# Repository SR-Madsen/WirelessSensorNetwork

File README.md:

# Wireless Sensor Network
STM32-based project for testing Internet of Things, Ethernet, RFID, and similar technologies.

## Repository Structure
This repository contains a folder for documentation, which includes datasheets and reference manuals used during the design phase as well as other tools and general documents. Additionally, there are folders for the Master board and Slave board. These further includes demo programs used for testing functionality that is possible to test on either the STM32F769-DISCO, STM32L412 Nucleo, or STM32WB55 Nucleo boards. The actual program used for each board is placed in a separate, aptly named, folder. The PCBs themselves are also found as KiCad projects within either the Master or Slave folder.

## Overview
The project will contain one large Master board with many functionalities and several small Slaves only used for measuring sensor values. The slaves are powered by a coin-cell battery, and will thus be in sleep mode most of the time. Occasionally, they will wake and retrieve sensor measurements, which are transmitted over 2.4 GHz ZigBee to the Master. The Master is supplied through USB and will, aside from receiving data from the Slaves, contain an RFID antenna used for detecting valid cards/keys, which allow the user to initiate a data transfer. This data transfer may be through USB or Ethernet, as the Master will host a small webpage containing the data from each Slave.

A full block diagram of the project can be found as draw.io files in the Documentation folder, but is also shown below. In the documentation folder, a LaTeX report can also be found.

## Hardware
The designed PCBs are shown below.

## Software
By using ST development kits and the STM32Cube ecosystem, preliminary software has been created for both the master and slave.

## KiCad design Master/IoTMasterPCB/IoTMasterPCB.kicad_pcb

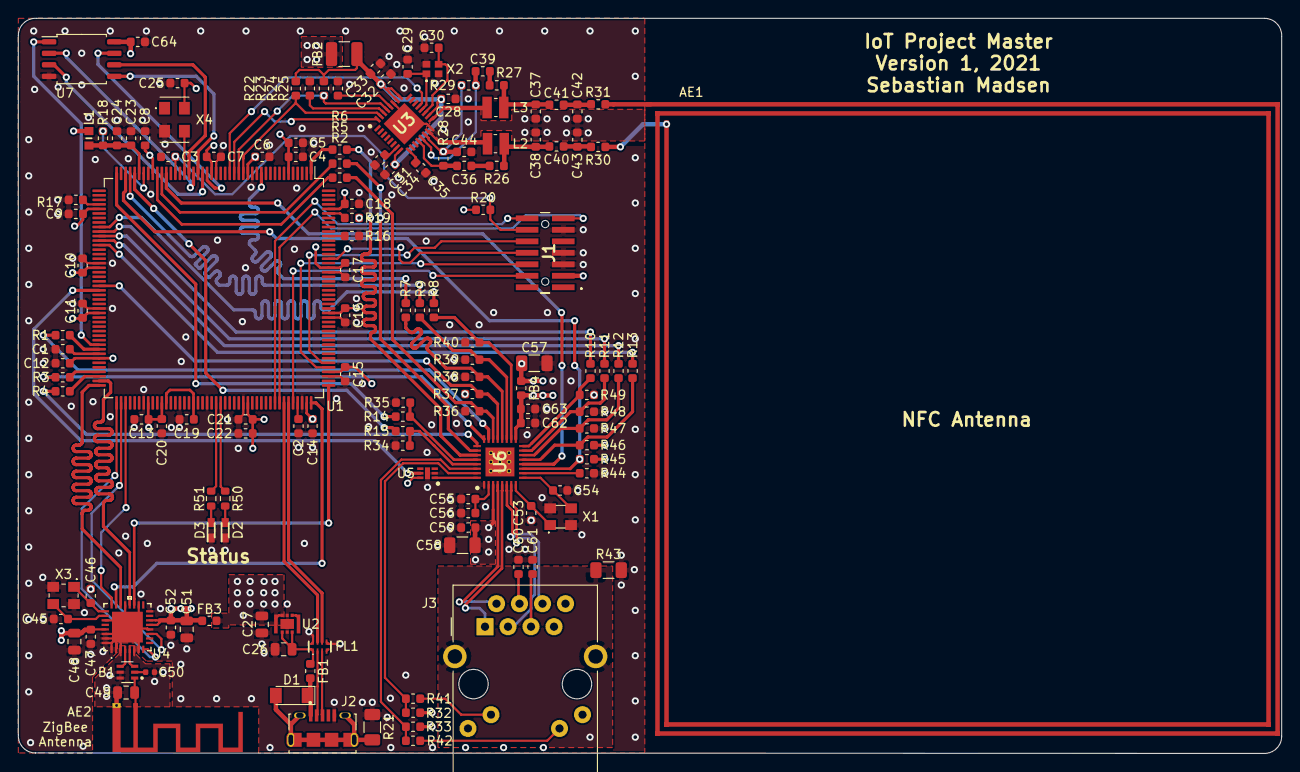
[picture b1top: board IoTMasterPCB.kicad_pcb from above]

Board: 4 copper layers, 139.5 x 81.2 mm, 143 parts (0 on the bottom side), 125 nets.

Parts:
AE1: NFC 13.56 MHz; NXP_NFC_13.56MHz
AE2: On-PCB; Texas_SWRA117D_2.4GHz_Left
B1: 2450FB15L0001E
C1, C2, C19: 2.2 µF; C_0603_1608Metric
C3, C4, C6, C7, C8, C9, C10, C11, C12, C13, C14, C15, C16, C17, C18, C20, C21, C23, C25, C28, C32, C34, C44, C47, C52, C64: 100 nF; C_0603_1608Metric
C5: 10 µF; C_0603_1608Metric
C22, C24, C33: 1 µF; C_0603_1608Metric
C26: 4.7 µF; C_0805_2012Metric
C27, C48, C51: 10 µF; C_0805_2012Metric
C29, C30: 15 pF; C_0603_1608Metric
C31, C35: 470 nF; C_0603_1608Metric
C36, C39: 1 nF; C_0603_1608Metric
C37, C38: 120 pF; C_0603_1608Metric
C40, C41: 56 pF; C_0603_1608Metric
C42, C43: 220 pF; C_0603_1608Metric
C45, C46: 22 pF; C_0603_1608Metric
C49: RF_MATCH; C_0805_2012Metric
C50: 22 pF C0G; C_0402_1005Metric
C53, C54: 27pF; C_0603_1608Metric
C55: 2.2uF; C_0603_1608Metric
C56, C59, C60, C61, C62: 100nF; C_0603_1608Metric
C57, C58: 22uF; C_1206_3216Metric
C63: 22uF; C_0603_1608Metric
D1: 5.6 V; D_MiniMELF
D2: 150060SS55040; 150060VS55040
D3: 150060VS55040
FB1: 120 @ 100 MHz; L_0603_1608Metric
FB2: 600R @ 100 MHz; L_1210_3225Metric
FB3: 600R @ 100 MHz; L_0603_1608Metric
FB4: 220R @ 100 MHz; L_0603_1608Metric
FL1: ECMF02-4CMX8; ECMF024CMX8
J1: M50-3610742R
J2: 10118194-0001LF
J3: RJMG1BD3B8K1ANR
L1: BK1608HS601-T
L2, L3: 470 nH; SRN2512R47M
R1, R2, R3, R4, R5, R6, R7, R8, R9, R10, R11, R12, R13, R14, R15: 33; R_0603_1608Metric
R16, R17, R19, R20: 10 kOhm; R_0603_1608Metric
R18: 47 Ohm; R_0603_1608Metric
R21: 0R; R_1206_3216Metric
R22, R23: 10k; R_0603_1608Metric
R24, R25, R32, R33, R37, R45, R46: 4.7k; R_0603_1608Metric
R26, R27: 12k; R_0603_1608Metric
R28, R29, R34, R35, R36, R38, R39, R40, R47, R48, R49: 1k; R_0603_1608Metric
R30, R31: 1.43; R_0603_1608Metric
R41, R42: 300; R_0603_1608Metric
R43: 0; R_1206_3216Metric
R44: 6.49k; R_0603_1608Metric
R50, R51: 150; R_0603_1608Metric
U1: STM32F469IITx; LQFP-176_24x24mm_P0.5mm
U2: MYRGP330100B21RA; MYRGP180100B21RA
U3: CLRC66303HNY
U4: AT86RF232-ZX
U5: MIC826TYMT-TR
U6: KSZ8081MNX
U7: W25Q32JVSS; SOIC-8_5.23x5.23mm_P1.27mm
X1: ECS-250-18-33B-CKY-TR; ECS-250-18-33B-CKY
X2: 27.12 MHz; ECS27121037AGNTR
X3: 16 MHz; ECS1601633BCKMTR
X4: ECS-5032MV-100-CN-TR; ECS5032MV250CNTR

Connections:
+3V3: C4.2, C5.2, C6.2, C7.2, C8.2, C9.2, C10.2, C11.2, C12.2, C13.2, C14.2, C15.2, C16.2, C17.2, C18.1, C20.2, C21.1, C22.1, C25.1, C27.2, C57.2, C64.2, FB2.2, FB3.2, FB4.1, J1.3, J3.L1, J3.L4, L1.1, R19.1, R20.1, U1.6, U1.15, U1.23, U1.36, U1.49, U1.62, U1.72, U1.82, U1.96, U1.99, U1.118, U1.131, U1.136, U1.149, U1.159, U1.172, U2.3, U2.8, U5.6, U7.8, X4.4
+5V: C26.2, FB1.1, FL1.1, U2.4, U2.6
/Ethernet/COL: R14.2, R35.2, U6.28
/Ethernet/CRS: R15.2, R34.2, U6.29
/Ethernet/LED1: R33.2, R42.2, U6.30
/Ethernet/LED2: R32.2, R41.2, U6.31
/Ethernet/RST: U5.1, U6.32
/Ethernet/RXD0: R10.2, R49.2, U6.16
/Ethernet/RXD1: R11.2, R48.2, U6.15
/Ethernet/RXD2: R12.2, R47.2, U6.14
/Ethernet/RXD3: R13.2, R46.2, U6.13
/Ethernet/RXN: J3.R6, U6.6
/Ethernet/RXP: J3.R3, U6.7
/Ethernet/RX_CLK: R9.2, R39.2, U6.19
/Ethernet/RX_DV: R8.2, R40.2, U6.18
/Ethernet/RX_ER: R7.2, R38.2, U6.20
/Ethernet/TXD0: R3.2, U6.24
/Ethernet/TXD1: R4.2, U6.25
/Ethernet/TXD2: R5.2, U6.26
/Ethernet/TXD3: R6.2, U6.27
/Ethernet/TXN: J3.R2, U6.4
/Ethernet/TXP: J3.R1, U6.5
/Ethernet/TX_CLK: R2.2, R36.2, U6.22
/Ethernet/TX_EN: R1.2, U6.23
/Ethernet/VDDA: C58.2, C59.1, C62.1, C63.1, FB4.2, R32.1, R33.1, R37.1, R45.1, R46.1, U6.3, U6.17
/Ethernet/XI: C54.1, U6.9, X1.3
/Ethernet/XO: C53.1, U6.8, X1.1
/MCU/12DSI: C19.2, U1.100, U1.106
/MCU/ETH_COL: R14.1, U1.44
/MCU/ETH_CRS: R15.1, U1.40
/MCU/ETH_INT: R37.2, U1.66, U6.21
/MCU/ETH_MDC: U1.33, U6.12
/MCU/ETH_MDIO: R45.2, U1.42, U6.11
/MCU/ETH_RXD0: R10.1, U1.54
/MCU/ETH_RXD1: R11.1, U1.55
/MCU/ETH_RXD2: R12.1, U1.56
/MCU/ETH_RXD3: R13.1, U1.57
/MCU/ETH_RX_CLK: R9.1, U1.41
/MCU/ETH_RX_DV: R8.1, U1.53
/MCU/ETH_RX_ER: R7.1, U1.12
/MCU/ETH_TXD0: R3.1, U1.85
/MCU/ETH_TXD1: R4.1, U1.86
/MCU/ETH_TXD2: R5.1, U1.34
/MCU/ETH_TXD3: R6.1, U1.1
/MCU/ETH_TX_CLK: R2.1, U1.35
/MCU/ETH_TX_EN: R1.1, U1.80
/MCU/I2C2_SCL: R23.1, U1.17, U3.29
/MCU/I2C2_SDA: R22.1, U1.16, U3.31
/MCU/JTCK: J1.6, U1.137
/MCU/JTDI: J1.10, U1.138
/MCU/JTDO: J1.8, U1.161
/MCU/JTMS: J1.4, U1.128
/MCU/NRST: C3.2, J1.12, R20.2, U1.31
/MCU/OSC_IN: U1.29, X4.3
/MCU/QSPI_BK1_CLK: U1.28, U7.6
/MCU/QSPI_BK1_IO0: U1.26, U7.5
/MCU/QSPI_BK1_IO1: U1.27, U7.2
/MCU/QSPI_BK1_IO2: U1.25, U7.3
/MCU/QSPI_BK1_IO3: U1.24, U7.7
/MCU/SPI2_MISO: U1.87, U4.20
/MCU/SPI2_MOSI: U1.88, U4.22
/MCU/SPI2_SCK: U1.133, U4.19
/MCU/UART_RX: J1.13, U1.125
/MCU/UART_TX: J1.14, U1.124
/MCU/USB_DN: FL1.7, U1.126
/MCU/USB_DP: FL1.6, U1.127
/MCU/VDDA: C23.1, C24.1, L1.2, R18.1, U1.39
/MCU/~ETH_RESET: U1.67, U5.5
/MCU/~QSPI_BK1_NCS: U1.79, U7.1
/MCU/~SPI2_NSS: U1.132, U4.23
/RFID/IRQ: U1.18, U3.32
/RFID/NFC_3V3: C28.2, C32.2, C33.2, C34.1, FB2.1, R22.2, R23.2, U3.8, U3.18, U3.25, U3.26
/RFID/PDOWN: U1.19, U3.21
/RFID/RXN: C39.1, R29.2, U3.13
/RFID/RXP: C36.1, R28.1, U3.12
/RFID/VMID: C44.1, R28.2, R29.1, U3.14
/ZigBee/IRQ: U1.91, U4.24
/ZigBee/SLP_TR: U1.90, U4.11
/ZigBee/XI: C46.1, U4.25, X3.1
/ZigBee/XO: C45.2, U4.26, X3.3
/ZigBee/ZB_3V3: C47.2, C48.2, C51.1, C52.1, FB3.1, U4.13, U4.14, U4.29
/ZigBee/~RST: U1.89, U4.8
GND: AE2.2, B1.5, B1.6, C1.1, C2.1, C3.1, C4.1, C5.1, C6.1, C7.1, C8.1, C9.1, C10.1, C11.1, C12.1, C13.1, C14.1, C15.1, C16.1, C17.1, C18.2, C19.1, C20.1, C21.2, C22.2, C23.2, C24.2, C25.2, C26.1, C27.1, C28.1, C29.1, C30.1, C31.2, C32.1, C33.1, C34.2, C35.1, C37.1, C38.2, C42.1, C43.2, C44.2, C45.1, C46.2, C47.1, C48.1, C49.2, C50.2, C51.2, C52.2, C53.2, C54.2, C55.1, C56.1, C57.1, C58.1, C59.2, C60.2, C61.2, C62.2, C63.2, C64.1, D2.1, D3.1, FL1.5, FL1.8, J1.5, J1.7, J1.11, J2.5, J3.R8, R16.1, R17.1, R21.1, R24.1, R25.1, R34.1, R35.1, R36.1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
GND1: D1.2, J2.S1, R21.2
unnamed: AE1.1, R31.2
unnamed: AE1.2, R30.2
unnamed: AE2.1, B1.1, C49.1
unnamed: B1.2, C50.1
unnamed: B1.3, U4.5
unnamed: B1.4, U4.4
unnamed: C1.2, U1.81
unnamed: C2.2, U1.129
unnamed: C29.2, U3.20, X2.1
unnamed: C30.2, U3.19, X2.3
unnamed: C31.1, U3.7
unnamed: C35.2, U3.9
unnamed: C36.2, R26.2
unnamed: C37.2, C40.2, L2.1, R26.1
unnamed: C38.1, C41.2, L3.2, R27.2
unnamed: C39.2, R27.1
unnamed: C40.1, C42.2, R30.1
unnamed: C41.1, C43.1, R31.1
unnamed: C55.2, C56.2, U6.2
unnamed: C60.1, J3.R4
unnamed: C61.1, J3.R5
unnamed: D1.1, FB1.2, J2.1
unnamed: D2.2, R50.1
unnamed: D3.2, R51.1
unnamed: FL1.2, J2.2
unnamed: FL1.3, J2.3
unnamed: J3.13, R43.1
unnamed: J3.L2, R42.1
unnamed: J3.L3, R41.1
unnamed: L2.2, U3.15
unnamed: L3.1, U3.17
unnamed: R16.2, U1.166
unnamed: R17.2, U1.48
unnamed: R18.2, U1.38
unnamed: R19.2, U1.171
unnamed: R24.2, U3.30
unnamed: R25.2, U3.28
unnamed: R44.1, U6.10
unnamed: R50.2, U1.112
unnamed: R51.2, U1.111
unnamed: U2.1, U2.7

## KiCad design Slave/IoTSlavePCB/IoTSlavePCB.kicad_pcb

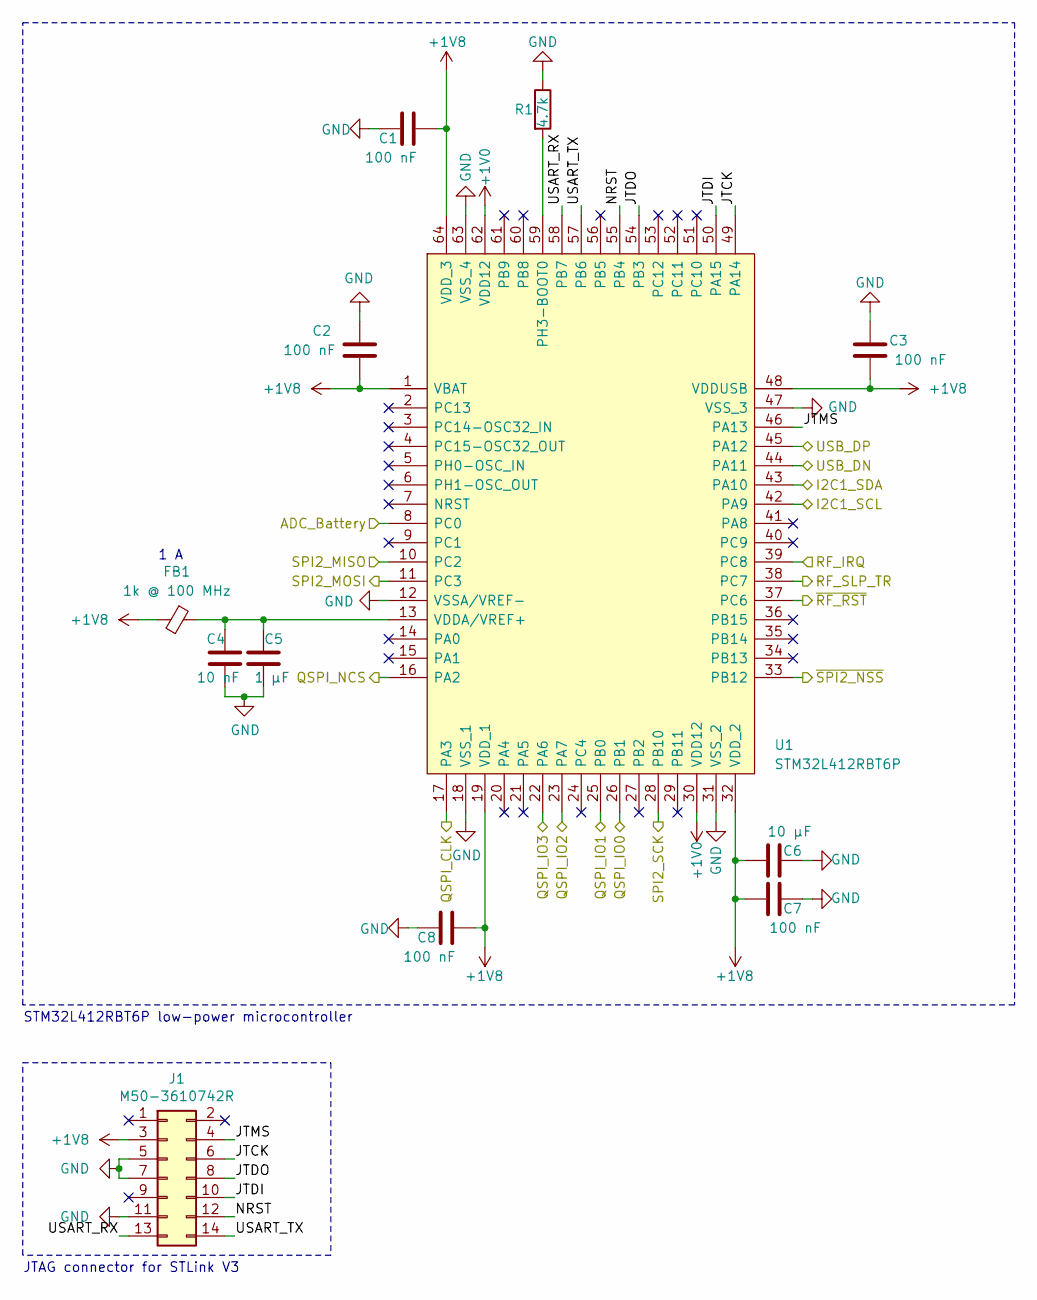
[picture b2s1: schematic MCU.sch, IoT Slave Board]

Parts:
C1, C2, C3, C7, C8: 100 nF; C_0603_1608Metric
C4: 10 nF; C_0603_1608Metric
C5: 1 µF; C_0805_2012Metric
C6: 10 µF; C_0805_2012Metric
FB1: 1k @ 100 MHz; L_0603_1608Metric
J1: M50-3610742R
R1: 4.7k; R_0603_1608Metric
U1: STM32L412RBT6P; Manufacturer_Part_Number STM32L412RBT6P; Mouser Part Number 511-STM32L412RBT6P

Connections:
+1V0: U1.30 (VDD12), U1.62 (VDD12); also elsewhere on the board
+1V8: C1.2, C2.2, C3.1, C6.1, C7.1, C8.2, FB1.2, J1.3, U1.1 (VBAT), U1.19 (VDD_1), U1.32 (VDD_2), U1.48 (VDDUSB), U1.64 (VDD_3); also elsewhere on the board
/MCU/ADC_Battery: U1.8 (PC0); also elsewhere on the board
/MCU/I2C1_SCL: U1.42 (PA9); also elsewhere on the board
/MCU/I2C1_SDA: U1.43 (PA10); also elsewhere on the board
/MCU/JTCK: J1.6, U1.49 (PA14)
/MCU/JTDI: J1.10, U1.50 (PA15)
/MCU/JTDO: J1.8, U1.54 (PB3)
/MCU/JTMS: J1.4, U1.46 (PA13)
/MCU/NRST: J1.12, U1.55 (PB4)
/MCU/QSPI_CLK: U1.17 (PA3); also elsewhere on the board
/MCU/QSPI_NCS: U1.16 (PA2); also elsewhere on the board
/MCU/RF_SLP_TR: U1.38 (PC7); also elsewhere on the board
/MCU/SPI2_MISO: U1.10 (PC2); also elsewhere on the board
/MCU/SPI2_MOSI: U1.11 (PC3); also elsewhere on the board
/MCU/SPI2_SCK: U1.28 (PB10); also elsewhere on the board
/MCU/USART_RX: J1.13, U1.58 (PB7)
/MCU/USART_TX: J1.14, U1.57 (PB6)
/MCU/USB_DN: U1.44 (PA11); also elsewhere on the board
/MCU/USB_DP: U1.45 (PA12); also elsewhere on the board
/MCU/~RF_RST: U1.37 (PC6); also elsewhere on the board
/MCU/~SPI2_NSS: U1.33 (PB12); also elsewhere on the board
/Memory/QSPI_DATA0: U1.26 (PB1); also elsewhere on the board
/Memory/QSPI_DATA1: U1.25 (PB0); also elsewhere on the board
/Memory/QSPI_DATA2: U1.23 (PA7); also elsewhere on the board
/Memory/QSPI_DATA3: U1.22 (PA6); also elsewhere on the board
/ZigBee/IRQ: U1.39 (PC8); also elsewhere on the board
GND: C1.1, C2.1, C3.2, C4.2, C5.2, C6.2, C7.2, C8.1, J1.5, J1.7, J1.11, R1.1, U1.12 (VSSA/VREF-), U1.18 (VSS_1), U1.31 (VSS_2), U1.47 (VSS_3), U1.63 (VSS_4); also elsewhere on the board
unnamed: C4.1, C5.1, FB1.1, U1.13 (VDDA/VREF+)
unnamed: R1.2, U1.59 (PH3-BOOT0)

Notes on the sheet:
JTAG connector for STLink V3
STM32L412RBT6P low-power microcontroller
1 A

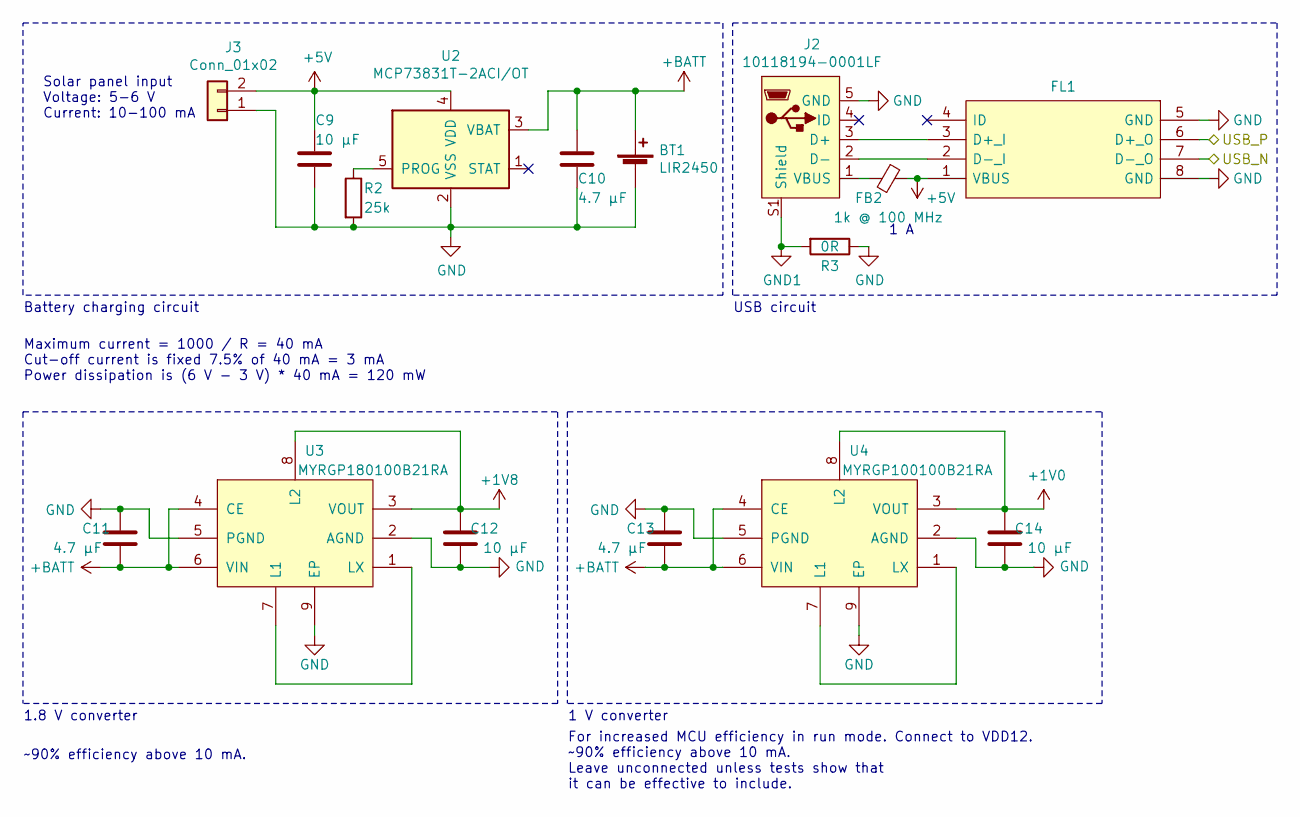
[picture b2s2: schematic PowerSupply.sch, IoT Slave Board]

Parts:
BT1: LIR2450; SMTU2450-LF
C9, C12, C14: 10 µF; C_0805_2012Metric
C10, C11, C13: 4.7 µF; C_0805_2012Metric
FB2: 1k @ 100 MHz; L_0603_1608Metric
FL1: ECMF02-4CMX8; ECMF024CMX8; Manufacturer_Part_Number ECMF02-4CMX8; Mouser Part Number 511-ECMF02-4CMX8
J2: 10118194-0001LF
J3: Conn_01x02; PinHeader_1x02_P1.27mm_Vertical
R2: 25k; R_0603_1608Metric
R3: 0R; R_1206_3216Metric
U2: MCP73831T-2ACI/OT; SOT-23-5
U3: MYRGP180100B21RA
U4: MYRGP100100B21RA; MYRGP180100B21RA

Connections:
+1V0: C14.2, U4.3 (VOUT), U4.8 (L2); also elsewhere on the board
+1V8: C12.2, U3.3 (VOUT), U3.8 (L2); also elsewhere on the board
+5V: C9.1, FB2.1, FL1.1 (VBUS), J3.2, U2.4 (VDD)
+BATT: BT1.1 (+), C10.1, C11.2, C13.2, U2.3 (VBAT), U3.4 (CE), U3.6 (VIN), U4.4 (CE), U4.6 (VIN); also elsewhere on the board
/MCU/USB_DN: FL1.7 (D-_O); also elsewhere on the board
/MCU/USB_DP: FL1.6 (D+_O); also elsewhere on the board
GND: BT1.2 (-), C9.2, C10.2, C11.1, C12.1, C13.1, C14.1, FL1.5 (GND), FL1.8 (GND), J2.5 (GND), J3.1, R2.2, R3.1, U2.2 (VSS), U3.2 (AGND), U3.5 (PGND), U3.9 (EP), U4.2 (AGND), U4.5 (PGND), U4.9 (EP); also elsewhere on the board
GND1: J2.S1 (Shield), R3.2
unnamed: FB2.2, J2.1 (VBUS)
unnamed: FL1.2 (D-_I), J2.2 (D-)
unnamed: FL1.3 (D+_I), J2.3 (D+)
unnamed: R2.1, U2.5 (PROG)
unnamed: U3.1 (LX), U3.7 (L1)
unnamed: U4.1 (LX), U4.7 (L1)

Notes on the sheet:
Solar panel input Voltage: 5-6 V Current: 10-100 mA
Maximum current = 1000 / R = 40 mA Cut-off current is fixed 7.5% of 40 mA = 3 mA Power dissipation is (6 V - 3 V) * 40 mA = 120 mW
Battery charging circuit
1.8 V converter
~~90% efficiency above 10 mA.
1 V converter
For increased MCU efficiency in run mode. Connect to VDD12. ~~90% efficiency above 10 mA. Leave unconnected unless tests show that it can be effective to include.
1 A
USB circuit

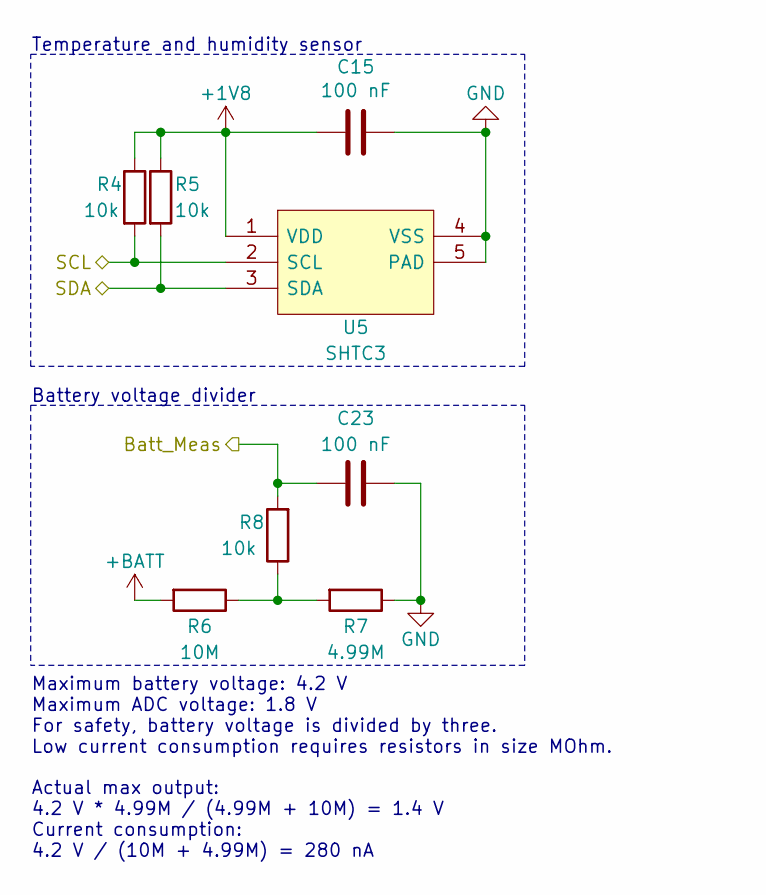
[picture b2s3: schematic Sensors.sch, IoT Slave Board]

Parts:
C15, C23: 100 nF; C_0603_1608Metric
R4, R5, R8: 10k; R_0603_1608Metric
R6: 10M; R_0603_1608Metric
R7: 4.99M; R_0603_1608Metric
U5: SHTC3; Manufacturer_Part_Number SHTC3; Mouser Part Number 403-SHTC3

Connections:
+1V8: C15.2, R4.1, R5.1, U5.1 (VDD); also elsewhere on the board
+BATT: R6.2; also elsewhere on the board
/MCU/ADC_Battery: C23.2, R8.2; also elsewhere on the board
/MCU/I2C1_SCL: R4.2, U5.2 (SCL); also elsewhere on the board
/MCU/I2C1_SDA: R5.2, U5.3 (SDA); also elsewhere on the board
GND: C15.1, C23.1, R7.1, U5.4 (VSS), U5.5 (PAD); also elsewhere on the board
unnamed: R6.1, R7.2, R8.1

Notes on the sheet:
Temperature and humidity sensor
Battery voltage divider
Maximum battery voltage: 4.2 V Maximum ADC voltage: 1.8 V For safety, battery voltage is divided by three. Low current consumption requires resistors in size MOhm.
Actual max output: 4.2 V * 4.99M / (4.99M + 10M) = 1.4 V Current consumption: 4.2 V / (10M + 4.99M) = 280 nA

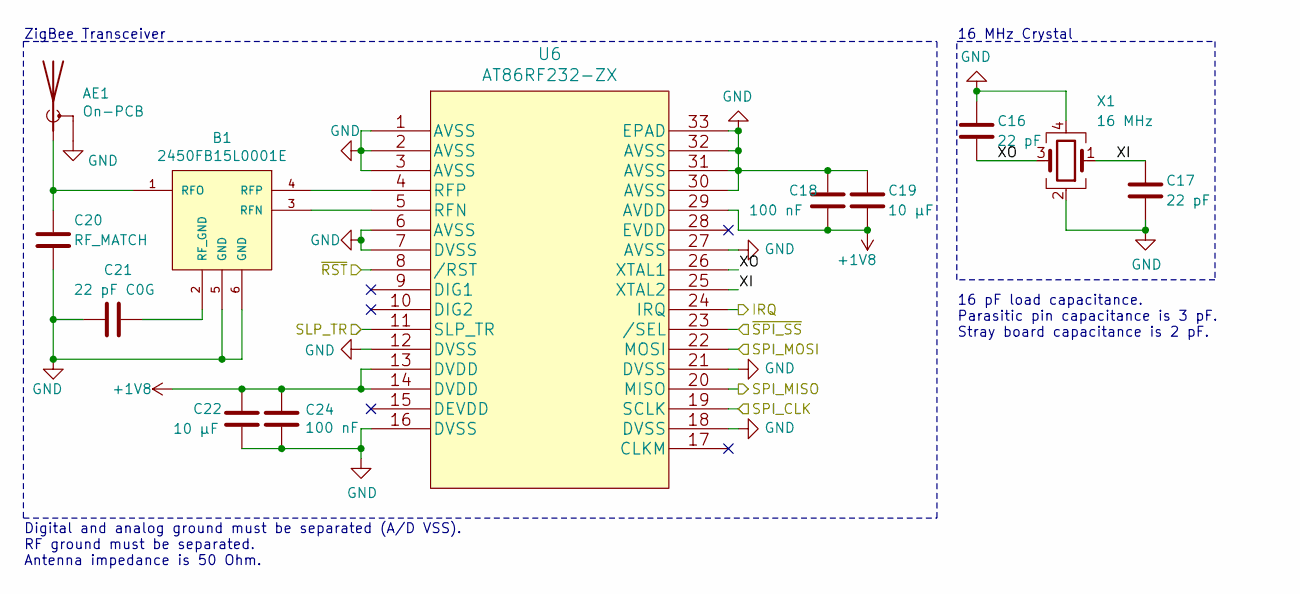
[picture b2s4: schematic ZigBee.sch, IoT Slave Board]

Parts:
AE1: On-PCB; Texas_SWRA117D_2.4GHz_Left
B1: 2450FB15L0001E
C16, C17: 22 pF; C_0603_1608Metric
C18, C24: 100 nF; C_0603_1608Metric
C19, C22: 10 µF; C_0805_2012Metric
C20: RF_MATCH; C_0805_2012Metric
C21: 22 pF C0G; C_0402_1005Metric; Part 500R07S220JV4 recommended
U6: AT86RF232-ZX
X1: 16 MHz; ECS1601633BCKMTR

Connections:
+1V8: C18.2, C19.2, C22.1, C24.1, U6.13 (DVDD), U6.14 (DVDD), U6.29 (AVDD); also elsewhere on the board
/MCU/RF_SLP_TR: U6.11 (SLP_TR); also elsewhere on the board
/MCU/SPI2_MISO: U6.20 (MISO); also elsewhere on the board
/MCU/SPI2_MOSI: U6.22 (MOSI); also elsewhere on the board
/MCU/SPI2_SCK: U6.19 (SCLK); also elsewhere on the board
/MCU/~RF_RST: U6.8 (/RST); also elsewhere on the board
/MCU/~SPI2_NSS: U6.23 (/SEL); also elsewhere on the board
/ZigBee/IRQ: U6.24 (IRQ); also elsewhere on the board
/ZigBee/XI: C17.1, U6.25 (XTAL2), X1.1
/ZigBee/XO: C16.2, U6.26 (XTAL1), X1.3
GND: AE1.2 (Shield), B1.5 (GND), B1.6 (GND), C16.1, C17.2, C18.1, C19.1, C20.2, C21.2, C22.2, C24.2, U6.1 (AVSS), U6.2 (AVSS), U6.3 (AVSS), U6.6 (AVSS), U6.7 (DVSS), U6.12 (DVSS), U6.16 (DVSS), U6.18 (DVSS), U6.21 (DVSS), U6.27 (AVSS), U6.30 (AVSS), U6.31 (AVSS), U6.32 (AVSS), U6.33 (EPAD), X1.2, X1.4; also elsewhere on the board
unnamed: AE1.1 (A), B1.1 (RFO), C20.1
unnamed: B1.2 (RF_GND), C21.1
unnamed: B1.3 (RFN), U6.5 (RFN)
unnamed: B1.4 (RFP), U6.4 (RFP)

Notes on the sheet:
16 pF load capacitance. Parasitic pin capacitance is 3 pF. Stray board capacitance is 2 pF.
16 MHz Crystal
Digital and analog ground must be separated (A/D VSS). RF ground must be separated. Antenna impedance is 50 Ohm.
ZigBee Transceiver

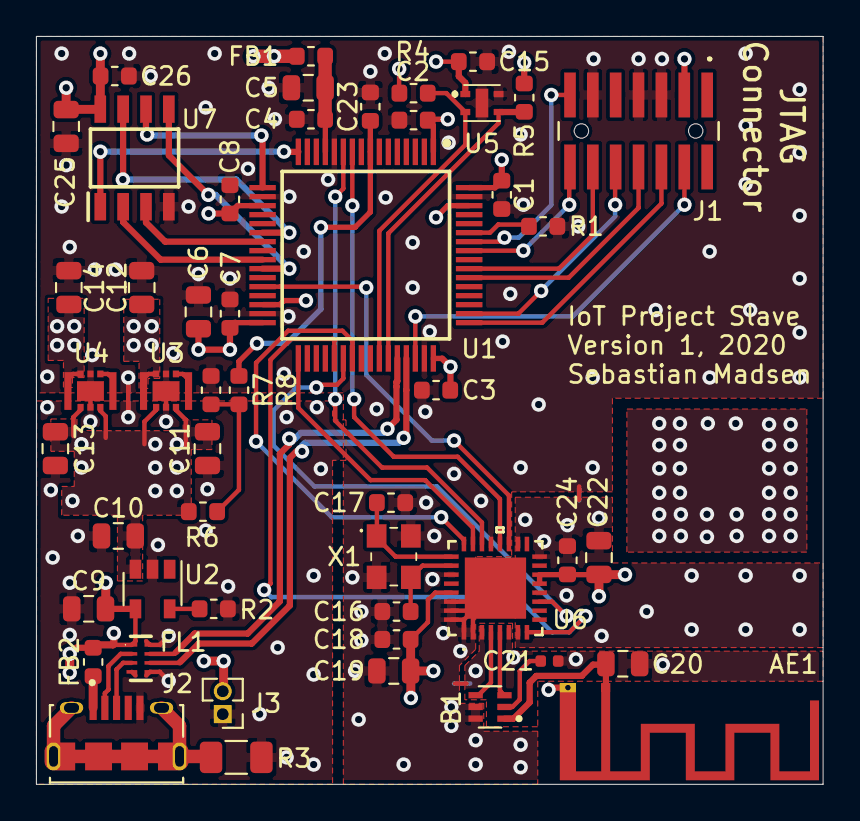
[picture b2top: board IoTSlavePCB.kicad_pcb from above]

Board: 4 copper layers, 43.7 x 41.5 mm, 51 parts (1 on the bottom side), 46 nets.

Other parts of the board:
C25: 10 µF; C_0805_2012Metric
C26: 100 nF; C_0603_1608Metric
U7: IS25WQ040-JNLE

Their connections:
+1V8: C25.2, C26.2, U7.8; also elsewhere on the board
/MCU/QSPI_CLK: U7.6; also elsewhere on the board
/MCU/QSPI_NCS: U7.1; also elsewhere on the board
/Memory/QSPI_DATA0: U7.5; also elsewhere on the board
/Memory/QSPI_DATA1: U7.2; also elsewhere on the board
/Memory/QSPI_DATA2: U7.3; also elsewhere on the board
/Memory/QSPI_DATA3: U7.7; also elsewhere on the board
GND: C25.1, C26.1, U7.4; also elsewhere on the board

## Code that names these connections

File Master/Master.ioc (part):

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Mcu.Name=STM32F469IITx
Mcu.Package=LQFP176
Mcu.UserName=STM32F469IITx
PA0/WKUP.Mode=MII
PA0/WKUP.Signal=ETH_CRS
PA1.Mode=MII
PA1.Signal=ETH_RX_CLK
PA10.Mode=Asynchronous
PA10.Signal=USART1_RX
PA13.Mode=JTAG_4_pins
PA13.Signal=SYS_JTMS-SWDIO
PA14.Mode=JTAG_4_pins
PA14.Signal=SYS_JTCK-SWCLK
PA15.Mode=JTAG_4_pins
PA15.Signal=SYS_JTDI
PA2.Mode=MII
PA2.Signal=ETH_MDIO
PA7.Mode=MII
PA7.Signal=ETH_RX_DV
PA9.Mode=Asynchronous
PA9.Signal=USART1_TX
PB0.Mode=MII
PB0.Signal=ETH_RXD2
PB1.Mode=MII
PB1.Signal=ETH_RXD3
PB10.Mode=Single Bank 1
PB10.Signal=QUADSPI_BK1_NCS
PB11.Mode=MII
PB11.Signal=ETH_TX_EN
PB12.Mode=MII
PB12.Signal=ETH_TXD0
PB13.Mode=MII
PB13.Signal=ETH_TXD1
PB14.Mode=Full_Duplex_Master
PB14.Signal=SPI2_MISO
PB15.Mode=Full_Duplex_Master
PB15.Signal=SPI2_MOSI
PB3.Mode=JTAG_4_pins
PB3.Signal=SYS_JTDO-SWO
PC1.Mode=MII
PC1.Signal=ETH_MDC
PC2.Mode=MII
PC2.Signal=ETH_TXD2
PC3.Mode=MII
PC3.Signal=ETH_TX_CLK
PC4.Mode=MII
PC4.Signal=ETH_RXD0
PC5.Mode=MII
PC5.Signal=ETH_RXD1
PD10.GPIOParameters=GPIO_Label
PD10.GPIO_Label=ZB_IRQ
PD10.Signal=GPIO_Input
PD8.GPIOParameters=PinState,GPIO_Label
PD8.GPIO_Label=ZB_RST
PD8.PinState=GPIO_PIN_SET
PD8.Signal=GPIO_Output
PD9.GPIOParameters=GPIO_Label
PD9.GPIO_Label=ZB_SLP_TR
PD9.Signal=GPIO_Output
PE2.Mode=MII
PE2.Signal=ETH_TXD3
PF0.GPIOParameters=GPIO_Pu
PF0.GPIO_Pu=GPIO_PULLUP
PF0.Mode=I2C
PF0.Signal=I2C2_SDA
PF1.GPIOParameters=GPIO_Pu
PF1.GPIO_Pu=GPIO_PULLUP
PF1.Mode=I2C
PF1.Signal=I2C2_SCL
PF10.Mode=Single Bank 1
PF10.Signal=QUADSPI_CLK
PF2.GPIOParameters=GPIO_Label
PF2.GPIO_Label=RFID_IRQ
PF2.Signal=GPIO_Input
PF3.GPIOParameters=GPIO_Label
PF3.GPIO_Label=RFID_PDOWN
PF3.Signal=GPIO_Output
PF6.Mode=Single Bank 1
PF6.Signal=QUADSPI_BK1_IO3
PF7.Mode=Single Bank 1
PF7.Signal=QUADSPI_BK1_IO2
PF8.Mode=Single Bank 1
PF8.Signal=QUADSPI_BK1_IO0
PF9.Mode=Single Bank 1
PF9.Signal=QUADSPI_BK1_IO1
PG0.GPIOParameters=GPIO_Label
PG0.GPIO_Label=ETH_INT
PG0.Signal=GPIO_Input
PG1.GPIOParameters=PinState,GPIO_Label
PG1.GPIO_Label=ETH_RESET
PG1.PinState=GPIO_PIN_SET
PG1.Signal=GPIO_Output
PH0/OSC_IN.Mode=HSE-External-Oscillator
PH0/OSC_IN.Signal=RCC_OSC_IN
PH1/OSC_OUT.Mode=HSE-External-Oscillator
PH1/OSC_OUT.Signal=RCC_OSC_OUT
PH3.Mode=MII
PH3.Signal=ETH_COL
PI0.Mode=NSS_Signal_Hard_Output
PI0.Signal=SPI2_NSS
PI1.Mode=Full_Duplex_Master
PI1.Signal=SPI2_SCK
PI10.Mode=Activate Rx Err signal
PI10.Signal=ETH_RX_ER
RCC.SYSCLKFreq_VALUE=180000000
RCC.SYSCLKSource=RCC_SYSCLKSOURCE_PLLCLK
board=custom

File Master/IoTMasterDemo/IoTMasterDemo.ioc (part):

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Mcu.Name=STM32F769NIHx
Mcu.Package=TFBGA216
Mcu.UserName=STM32F769NIHx
PA0/WKUP.GPIOParameters=GPIO_Label
PA0/WKUP.GPIO_Label=B_USER [B1]
PA0/WKUP.Signal=GPXTI0
PA1.GPIOParameters=GPIO_Label
PA1.GPIO_Label=RMII_REF_CLK [LAN8742A-CZ-TR_REFCLK0]
PA1.Mode=RMII
PA1.Signal=ETH_REF_CLK
PA10.GPIOParameters=GPIO_Label
PA10.GPIO_Label=VCP_RX 
PA10.Mode=Asynchronous
PA10.Signal=USART1_RX
PA11.GPIOParameters=GPIO_Label
PA11.GPIO_Label=SPI2_NSS
PA11.Signal=SPI2_NSS
PA12.GPIOParameters=GPIO_Speed,GPIO_PuPd,GPIO_Label,GPIO_Mode
PA12.GPIO_Label=ARD_D13/SCK
PA12.GPIO_Mode=GPIO_MODE_AF_PP
PA12.GPIO_PuPd=GPIO_NOPULL
PA12.GPIO_Speed=GPIO_SPEED_FREQ_LOW
PA12.Signal=SPI2_SCK
PA13.GPIOParameters=GPIO_Label
PA13.GPIO_Label=SWDIO
PA13.Mode=Serial_Wire
PA13.Signal=SYS_JTMS-SWDIO
PA14.GPIOParameters=GPIO_Label
PA14.GPIO_Label=SWCLK
PA14.Mode=Serial_Wire
PA14.Signal=SYS_JTCK-SWCLK
PA15.GPIOParameters=GPIO_Label
PA15.GPIO_Label=CEC
PA15.Signal=CEC
PA2.GPIOParameters=GPIO_Label
PA2.GPIO_Label=RMII_MDIO [LAN8742A-CZ-TR_MDIO]
PA2.Mode=RMII
PA2.Signal=ETH_MDIO
PA3.GPIOParameters=GPIO_Label
PA3.GPIO_Label=ULPI_D0 [USB3320C-EZK_D0]
PA3.Signal=USB_OTG_HS_ULPI_D0
PA4.GPIOParameters=GPIO_Label
PA4.GPIO_Label=ARD_A1
PA4.Signal=ADCx_IN4
PA5.GPIOParameters=GPIO_Label
PA5.GPIO_Label=ULPI_CLK [USB3320C-EZK_CLKOUT]
PA5.Signal=USB_OTG_HS_ULPI_CK
PA6.GPIOParameters=GPIO_Label
PA6.GPIO_Label=ARD_A0
PA6.Signal=ADCx_IN6
PA7.GPIOParameters=GPIO_Label
PA7.GPIO_Label=RMII_CRS_DV [LAN8742A-CZ-TR_CRS_DV]
PA7.Mode=RMII
PA7.Signal=ETH_CRS_DV
PA8.GPIOParameters=GPIO_Label
PA8.GPIO_Label=CEC_CLK [TP2]
PA8.Mode=Clock-out-1
PA8.Signal=RCC_MCO_1
PA9.GPIOParameters=GPIO_Speed,GPIO_PuPd,GPIO_Label,GPIO_Mode
PA9.GPIO_Label=VCP_TX [STM32F103CBT6_PA3]
PA9.GPIO_Mode=GPIO_MODE_AF_PP
PA9.GPIO_PuPd=GPIO_NOPULL
PA9.GPIO_Speed=GPIO_SPEED_FREQ_LOW
PA9.Mode=Asynchronous
PA9.Signal=USART1_TX
PB0.GPIOParameters=GPIO_Label
PB0.GPIO_Label=ULPI_D1 [USB3320C-EZK_D1]
PB0.Signal=USB_OTG_HS_ULPI_D1
PB1.GPIOParameters=GPIO_Label
PB1.GPIO_Label=ULPI_D2 [USB3320C-EZK_D2]
PB1.Signal=USB_OTG_HS_ULPI_D2
PB10.GPIOParameters=GPIO_Label
PB10.GPIO_Label=ULPI_D3 [USB3320C-EZK_D3]
PB10.Signal=USB_OTG_HS_ULPI_D3
PB11.GPIOParameters=GPIO_Label
PB11.GPIO_Label=ULPI_D4 [USB3320C-EZK_D4]
PB11.Signal=USB_OTG_HS_ULPI_D4
PB12.GPIOParameters=GPIO_Label
PB12.GPIO_Label=ULPI_D5 [USB3320C-EZK_D5]
PB12.Signal=USB_OTG_HS_ULPI_D5
PB13.GPIOParameters=GPIO_Label
PB13.GPIO_Label=ULPI_D6 [USB3320C-EZK_D6]
PB13.Signal=USB_OTG_HS_ULPI_D6
PB14.GPIOParameters=GPIO_Speed,GPIO_PuPd,GPIO_Label,GPIO_Mode
PB14.GPIO_Label=ARDUINO MISO/D12
PB14.GPIO_Mode=GPIO_MODE_AF_PP
PB14.GPIO_PuPd=GPIO_NOPULL
PB14.GPIO_Speed=GPIO_SPEED_FREQ_LOW
PB14.Signal=SPI2_MISO
PB15.GPIOParameters=GPIO_Speed,GPIO_PuPd,GPIO_Label,GPIO_Mode
PB15.GPIO_Label=ARDUINO MOSI/PWM/D11
PB15.GPIO_Mode=GPIO_MODE_AF_PP
PB15.GPIO_PuPd=GPIO_NOPULL
PB15.GPIO_Speed=GPIO_SPEED_FREQ_LOW
PB15.Signal=SPI2_MOSI
PB2.Mode=Single Bank 1
PB2.Signal=QUADSPI_CLK
PB3.GPIOParameters=GPIO_Label
PB3.GPIO_Label=uSD_D2
PB3.Signal=SDMMC2_D2
PB4.GPIOParameters=GPIO_Label
PB4.GPIO_Label=uSD_D3
PB4.Signal=SDMMC2_D3
PB5.GPIOParameters=GPIO_Label
PB5.GPIO_Label=ULPI_D7 [USB3320C-EZK_D7]
PB5.Signal=USB_OTG_HS_ULPI_D7
PB6.GPIOParameters=GPIO_Label
PB6.GPIO_Label=QSPI_NCS [N25Q128A13EF840E_S]
PB6.Mode=Single Bank 1
PB6.Signal=QUADSPI_BK1_NCS
PB7.GPIOParameters=GPIO_Label
PB7.GPIO_Label=AUDIO_SDA [WM8994ECS/R_SDA]
PB7.Signal=I2C4_SDA
PB8.GPIOParameters=GPIO_Speed,GPIO_PuPd,GPIO_Label,GPIO_Mode
PB8.GPIO_Label=ARDUINO SCL/D15
PB8.GPIO_Mode=GPIO_MODE_AF_OD
PB8.GPIO_PuPd=GPIO_NOPULL
PB8.GPIO_Speed=GPIO_SPEED_FREQ_LOW
PB8.Signal=I2C1_SCL
PB9.GPIOParameters=GPIO_Speed,GPIO_PuPd,GPIO_Label,GPIO_Mode
PB9.GPIO_Label=ARDUINO SDA/D14
PB9.GPIO_Mode=GPIO_MODE_AF_OD
PB9.GPIO_PuPd=GPIO_NOPULL
PB9.GPIO_Speed=GPIO_SPEED_FREQ_LOW
PB9.Signal=I2C1_SDA
PC0.GPIOParameters=GPIO_Label
PC0.GPIO_Label=ULPI_STP [USB3320C-EZK_STP]
PC0.Signal=USB_OTG_HS_ULPI_STP
PC1.GPIOParameters=GPIO_Label
PC1.GPIO_Label=RMII_MDC [LAN8742A-CZ-TR_MDC]
PC1.Mode=RMII
PC1.Signal=ETH_MDC
PC10.GPIOParameters=GPIO_Label
PC10.GPIO_Label=QSPI_D1 [MT25QL512ABB1EW9_DQ1]
PC10.Mode=Single Bank 1
PC10.Signal=QUADSPI_BK1_IO1
PC11.GPIOParameters=GPIO_Label
PC11.GPIO_Label=DFSDM_DATIN5 [TP5]
PC11.Signal=S_DATAIN5DFSDM1
PC12.GPIOParameters=GPIO_Label
PC12.GPIO_Label=WIFI_RX
PC12.Mode=Asynchronous
PC12.Signal=UART5_TX
PC14/OSC32_IN.GPIOParameters=GPIO_Label
PC14/OSC32_IN.GPIO_Label=RCC_OSC32_IN
PC14/OSC32_IN.Mode=LSE-External-Oscillator
PC14/OSC32_IN.Signal=RCC_OSC32_IN
PC15/OSC32_OUT.GPIOParameters=GPIO_Label
PC15/OSC32_OUT.GPIO_Label=RCC_OSC32_OUT
PC15/OSC32_OUT.Mode=LSE-External-Oscillator
PC15/OSC32_OUT.Signal=RCC_OSC32_OUT
PC2.GPIOParameters=GPIO_Label
PC2.GPIO_Label=ARD_A2
PC2.Signal=ADCx_IN12
PC4.GPIOParameters=GPIO_Label
PC4.GPIO_Label=RMII_RXD0 [LAN8742A-CZ-TR_RXD0]
PC4.Mode=RMII
PC4.Signal=ETH_RXD0
PC5.GPIOParameters=GPIO_Label
PC5.GPIO_Label=RMII_RXD1 [LAN8742A-CZ-TR_RXD1]
PC5.Mode=RMII
PC5.Signal=ETH_RXD1
PC6.GPIOParameters=GPIO_Label
PC6.GPIO_Label=ARDUINO TX/D1
PC6.Mode=Asynchronous
PC6.Signal=USART6_TX
PC7.GPIOParameters=GPIO_Label
PC7.GPIO_Label=ARD_D0/RX
PC7.Mode=Asynchronous
PC7.Signal=USART6_RX
PC8.GPIOParameters=GPIO_Label
PC8.GPIO_Label=ARD_D5/PWM
PC8.Signal=S_TIM3_CH3
PC9.GPIOParameters=GPIO_Label
PC9.GPIO_Label=QSPI_D0 [N25Q128A13EF840E_DQ0]
PC9.Mode=Single Bank 1
PC9.Signal=QUADSPI_BK1_IO0
PD0.GPIOParameters=GPIO_Label
PD0.GPIO_Label=FMC_D2 [MT48LC4M32B2B5-6A_DQ2]
PD0.Signal=FMC_D2_DA2
PD1.GPIOParameters=GPIO_Label
PD1.GPIO_Label=FMC_D3 [MT48LC4M32B2B5-6A_DQ3]
PD1.Signal=FMC_D3_DA3
PD10.GPIOParameters=GPIO_Label
PD10.GPIO_Label=FMC_D15 [MT48LC4M32B2B5-6A_DQ15]
PD10.Signal=FMC_D15_DA15
PD11.GPIOParameters=GPIO_Label
PD11.GPIO_Label=SPDIF_TX [TP20]
PD11.Signal=SAI2_SD_A
PD12.GPIOParameters=GPIO_Label
PD12.GPIO_Label=AUDIO_SCL [WM8994ECS/R_SCLK]
PD12.Signal=I2C4_SCL
PD13.GPIOParameters=GPIO_Label
PD13.GPIO_Label=QSPI_D3 [N25Q128A13EF840E_DQ3]
PD13.Mode=Single Bank 1
PD13.Signal=QUADSPI_BK1_IO3
PD14.GPIOParameters=GPIO_Label
PD14.GPIO_Label=FMC_D0 [MT48LC4M32B2B5-6A_DQ0]
PD14.Signal=FMC_D0_DA0
PD15.GPIOParameters=GPIO_Label
PD15.GPIO_Label=FMC_D1 [MT48LC4M32B2B5-6A_DQ1]
PD15.Signal=FMC_D1_DA1
PD2.GPIOParameters=GPIO_Label
PD2.GPIO_Label=WIFI_TX
PD2.Mode=Asynchronous
PD2.Signal=UART5_RX
PD3.GPIOParameters=GPIO_Label
PD3.GPIO_Label=DFSDM_CKOUT [TP102]
PD3.Signal=S_CKOUTDFSDM1
PD4.GPIOParameters=GPIO_Label
PD4.GPIO_Label=OTG_FS_OverCurrent [STMPS2141STR_Fault]
PD4.Signal=GPIO_Input
PD5.GPIOParameters=GPIO_Label
PD5.GPIO_Label=RMII_RXER[LAN8742A-CZ-TR_RXERR]
PD5.Signal=GPIO_Input
PD6.GPIOParameters=GPIO_Label
PD6.GPIO_Label=uSD_CLK
PD6.Signal=SDMMC2_CK
PD7.GPIOParameters=GPIO_Label
PD7.GPIO_Label=uSD_CMD
PD7.Signal=SDMMC2_CMD
PD8.GPIOParameters=GPIO_Label
PD8.GPIO_Label=FMC_D13 [MT48LC4M32B2B5-6A_DQ13]
PD8.Signal=FMC_D13_DA13
PD9.GPIOParameters=GPIO_Label
PD9.GPIO_Label=FMC_D14 [MT48LC4M32B2B5-6A_DQ14]
PD9.Signal=FMC_D14_DA14
PE0.GPIOParameters=GPIO_Label
PE0.GPIO_Label=FMC_NBL0 [MT48LC4M32B2B5-6A_DQM0]
PE0.Signal=FMC_NBL0
PE1.GPIOParameters=GPIO_Label
PE1.GPIO_Label=FMC_NBL1 [MT48LC4M32B2B5-6A_DQM1]
PE1.Signal=FMC_NBL1
PE10.GPIOParameters=GPIO_Label
PE10.GPIO_Label=FMC_D7 [MT48LC4M32B2B5-6A_DQ7]
PE10.Signal=FMC_D7_DA7
PE11.GPIOParameters=GPIO_Label
PE11.GPIO_Label=FMC_D8 [MT48LC4M32B2B5-6A_DQ8]
PE11.Signal=FMC_D8_DA8
PE12.GPIOParameters=GPIO_Label
PE12.GPIO_Label=FMC_D9 [MT48LC4M32B2B5-6A_DQ9]
PE12.Signal=FMC_D9_DA9
PE13.GPIOParameters=GPIO_Label
PE13.GPIO_Label=FMC_D10 [MT48LC4M32B2B5-6A_DQ10]
PE13.Signal=FMC_D10_DA10
PE14.GPIOParameters=GPIO_Label
PE14.GPIO_Label=FMC_D11 [MT48LC4M32B2B5-6A_DQ11]
PE14.Signal=FMC_D11_DA11
PE15.GPIOParameters=GPIO_Label
PE15.GPIO_Label=FMC_D12 [MT48LC4M32B2B5-6A_DQ12]
PE15.Signal=FMC_D12_DA12
PE2.GPIOParameters=GPIO_Label
PE2.GPIO_Label=QSPI_D2 [N25Q128A13EF840E_DQ2]
PE2.Mode=Single Bank 1
PE2.Signal=QUADSPI_BK1_IO2
PE3.GPIOParameters=GPIO_Label
PE3.GPIO_Label=SAI1_SDB [WM8994ECS/R_ADCDAT1]
PE3.Signal=SAI1_SD_B
PE4.GPIOParameters=GPIO_Label
PE4.GPIO_Label=SAI1_FSA [WM8994ECS/R_LRCLK1]
PE4.Signal=SAI1_FS_A
PE5.GPIOParameters=GPIO_Label
PE5.GPIO_Label=SAI1_SCKA [WM8994ECS/R_BCLK1]
PE5.Signal=SAI1_SCK_A
PE6.GPIOParameters=GPIO_Label
PE6.GPIO_Label=SAI1_SDA [WM8994ECS/R_DACDAT1]
PE6.Signal=SAI1_SD_A
PE7.GPIOParameters=GPIO_Label
PE7.GPIO_Label=FMC_D4 [MT48LC4M32B2B5-6A_DQ4]
PE7.Signal=FMC_D4_DA4
PE8.GPIOParameters=GPIO_Label
PE8.GPIO_Label=FMC_D5 [MT48LC4M32B2B5-6A_DQ5]
PE8.Signal=FMC_D5_DA5
PE9.GPIOParameters=GPIO_Label
PE9.GPIO_Label=FMC_D6 [MT48LC4M32B2B5-6A_DQ6]
PE9.Signal=FMC_D6_DA6
PF0.GPIOParameters=GPIO_Label
PF0.GPIO_Label=FMC_A0 [MT48LC4M32B2B5-6A_A0]
PF0.Signal=FMC_A0
PF1.GPIOParameters=GPIO_Label
PF1.GPIO_Label=FMC_A1 [MT48LC4M32B2B5-6A_A1]
PF1.Signal=FMC_A1
PF10.GPIOParameters=GPIO_PuPd,GPIO_Label,GPIO_Mode
PF10.GPIO_Label=ARDUINO A1
PF10.GPIO_Mode=GPIO_MODE_ANALOG
PF10.GPIO_PuPd=GPIO_NOPULL
PF10.Signal=ADC3_IN8
PF11.GPIOParameters=GPIO_Label
PF11.GPIO_Label=FMC_SDNRAS [MT48LC4M32B2B5-6A_RAS]
PF11.Signal=FMC_SDNRAS

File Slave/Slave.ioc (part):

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Mcu.Name=STM32L412RBTxP
Mcu.Package=LQFP64
Mcu.UserName=STM32L412RBTxP
PA10.GPIOParameters=GPIO_Pu
PA10.GPIO_Pu=GPIO_PULLUP
PA10.Mode=I2C
PA10.Signal=I2C1_SDA
PA13\ (JTMS/SWDIO).Mode=JTAG_5_pins
PA13\ (JTMS/SWDIO).Signal=SYS_JTMS-SWDIO
PA14\ (JTCK/SWCLK).Mode=JTAG_5_pins
PA14\ (JTCK/SWCLK).Signal=SYS_JTCK-SWCLK
PA15\ (JTDI).Mode=JTAG_5_pins
PA15\ (JTDI).Signal=SYS_JTDI
PA2.Mode=Single Bank 1
PA2.Signal=QUADSPI_BK1_NCS
PA3.Mode=Single Bank 1
PA3.Signal=QUADSPI_CLK
PA6.Mode=Single Bank 1
PA6.Signal=QUADSPI_BK1_IO3
PA7.Mode=Single Bank 1
PA7.Signal=QUADSPI_BK1_IO2
PA9.GPIOParameters=GPIO_Pu
PA9.GPIO_Pu=GPIO_PULLUP
PA9.Mode=I2C
PA9.Signal=I2C1_SCL
PB0.Mode=Single Bank 1
PB0.Signal=QUADSPI_BK1_IO1
PB1.Mode=Single Bank 1
PB1.Signal=QUADSPI_BK1_IO0
PB10.Mode=Full_Duplex_Master
PB10.Signal=SPI2_SCK
PB12.Mode=NSS_Signal_Hard_Output
PB12.Signal=SPI2_NSS
PB3\ (JTDO/TRACESWO).Mode=JTAG_5_pins
PB3\ (JTDO/TRACESWO).Signal=SYS_JTDO-SWO
PB4\ (NJTRST).Mode=JTAG_5_pins
PB4\ (NJTRST).Signal=SYS_JTRST
PB6.Mode=Asynchronous
PB6.Signal=USART1_TX
PB7.Mode=Asynchronous
PB7.Signal=USART1_RX
PC0.Signal=ADCx_IN1
PC2.Mode=Full_Duplex_Master
PC2.Signal=SPI2_MISO
PC3.Mode=Full_Duplex_Master
PC3.Signal=SPI2_MOSI
PC6.GPIOParameters=GPIO_PuPd,GPIO_Label
PC6.GPIO_Label=RF_RST
PC6.GPIO_PuPd=GPIO_PULLUP
PC6.Signal=GPIO_Output
PC7.GPIOParameters=GPIO_PuPd,GPIO_Label
PC7.GPIO_Label=RF_SLP_TR
PC7.GPIO_PuPd=GPIO_PULLDOWN
PC7.Signal=GPIO_Output
PC8.GPIOParameters=GPIO_PuPd,GPIO_Label
PC8.GPIO_Label=RF_IRQ
PC8.GPIO_PuPd=GPIO_PULLDOWN
PC8.Signal=GPIO_Input
RCC.HSE_VALUE=8000000
RCC.SYSCLKFreq_VALUE=4000000
board=custom

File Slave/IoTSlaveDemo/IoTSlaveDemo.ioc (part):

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Mcu.Name=STM32L412RBTxP
Mcu.Package=LQFP64
Mcu.UserName=STM32L412RBTxP
PA13\ (JTMS/SWDIO).GPIOParameters=GPIO_Label
PA13\ (JTMS/SWDIO).GPIO_Label=TMS
PA13\ (JTMS/SWDIO).Mode=Serial_Wire
PA13\ (JTMS/SWDIO).Signal=SYS_JTMS-SWDIO
PA14\ (JTCK/SWCLK).GPIOParameters=GPIO_Label
PA14\ (JTCK/SWCLK).GPIO_Label=TCK
PA14\ (JTCK/SWCLK).Mode=Serial_Wire
PA14\ (JTCK/SWCLK).Signal=SYS_JTCK-SWCLK
PA2.GPIOParameters=GPIO_Speed,GPIO_PuPd,GPIO_Label
PA2.GPIO_Label=USART_TX
PA2.GPIO_PuPd=GPIO_NOPULL
PA2.GPIO_Speed=GPIO_SPEED_FREQ_VERY_HIGH
PA2.Mode=Asynchronous
PA2.Signal=USART2_TX
PA3.GPIOParameters=GPIO_Speed,GPIO_PuPd,GPIO_Label
PA3.GPIO_Label=USART_RX
PA3.GPIO_PuPd=GPIO_NOPULL
PA3.GPIO_Speed=GPIO_SPEED_FREQ_VERY_HIGH
PA3.Mode=Asynchronous
PA3.Signal=USART2_RX
PA4.GPIOParameters=GPIO_Label
PA4.GPIO_Label=SMPS_EN [ADP5301ACBZ_VEN]
PA4.Signal=GPIO_Output
PA5.GPIOParameters=GPIO_Speed,GPIO_PuPd,GPIO_Label,GPIO_ModeDefaultOutputPP
PA5.GPIO_Label=SMPS_V1
PA5.GPIO_ModeDefaultOutputPP=GPIO_MODE_OUTPUT_PP
PA5.GPIO_PuPd=GPIO_NOPULL
PA5.GPIO_Speed=GPIO_SPEED_FREQ_LOW
PA5.Signal=GPIO_Output
PA6.GPIOParameters=GPIO_PuPd,GPIO_Label
PA6.GPIO_Label=SMPS_PG [ADP5301ACBZ_OUTOK]
PA6.GPIO_PuPd=GPIO_PULLUP
PA6.Signal=GPIO_Input
PA7.GPIOParameters=GPIO_Label
PA7.GPIO_Label=SMPS_SW [TS3A44159PWR_IN1_2]
PA7.Signal=GPIO_Output
PB13.GPIOParameters=GPIO_Label
PB13.GPIO_Label=LD4 [green Led]
PB13.Signal=GPIO_Output
PB3\ (JTDO/TRACESWO).GPIOParameters=GPIO_Label
PB3\ (JTDO/TRACESWO).GPIO_Label=SWO
PB3\ (JTDO/TRACESWO).Signal=SYS_JTDO-SWO
PC13.GPIOParameters=GPIO_PuPd,GPIO_Label,GPIO_ModeDefaultEXTI
PC13.GPIO_Label=B1 [Blue PushButton]
PC13.GPIO_ModeDefaultEXTI=GPIO_MODE_IT_FALLING
PC13.GPIO_PuPd=GPIO_NOPULL
PC13.Signal=GPXTI13
PC14-OSC32_IN\ (PC14).Mode=LSE-External-Oscillator
PC14-OSC32_IN\ (PC14).Signal=RCC_OSC32_IN
PC15-OSC32_OUT\ (PC15).Mode=LSE-External-Oscillator
PC15-OSC32_OUT\ (PC15).Signal=RCC_OSC32_OUT
PH0-OSC_IN\ (PH0).GPIOParameters=GPIO_Label
PH0-OSC_IN\ (PH0).GPIO_Label=MCO
PH0-OSC_IN\ (PH0).Mode=HSE-External-Clock-Source
PH0-OSC_IN\ (PH0).Signal=RCC_OSC_IN
PH1-OSC_OUT\ (PH1).Signal=RCC_OSC_OUT
RCC.HSE_VALUE=8000000
RCC.SYSCLKFreq_VALUE=80000000
RCC.SYSCLKSource=RCC_SYSCLKSOURCE_PLLCLK
board=NUCLEO-L412RB-P
boardIOC=true

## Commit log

2020-10-31 STM32CubeMX files added for both master and slave.
2020-11-01 Added block diagrams for both boards, modifications to CubeMX file.
2020-11-01 Setup schematics for both master and slave. Minor changes to MX configurations. Started design of slaves.
2020-11-06 Continued work on slaves. Added sensor and begun work on ZigBee transceiver.
2020-11-23 Finished slave schematics, including memory and Zigbee Transceiver. Further work on PCB, well underway.
2020-11-24 Made more connections on PCB, some optimizations. Added silk screen text.
2020-11-24 Everything placed. Only needs final routes and optimization.
2020-11-26 Further PCB work.
2020-11-27 Prettified PCB, some changes to routes and planes for performance.
2020-11-28 Change for clarity.
2020-11-28 Added battery voltage measurement circuit. Optimizations to antenna and general component placement.
2020-11-28 Updated Master Board schematics. Added JTAG connector.
2020-12-05 Added some components for Master Board schematic.
2020-12-05 Work on Master Board schematics; added full Zigbee. Added RFID module. Added USB/power supply, as well as MCU decoupling.
2020-12-07 Added flash storage, work on RFID front-end.
2020-12-10 Finished RFID module sans antenna footprint. Added KSZ8081MNX and hierarchial connections.
2020-12-11 Finished RFID and Ethernet circuits.
2020-12-18 Minor changes to schematics, started work on PCB layout.
2020-12-23 Placed STM32 on Master PCB. Corrected I2C naming.
2021-01-11 Added datasheets, reference manuals, and application notes for used ICs.
2021-01-21 More work on PCB layout, as wel as generation of LWIP (Ethernet) demo program for Master.
2021-01-28 Minor changes to schematic, finished placing all components, only minor fixes needed to PCB now.
2021-02-08 Finished Master PCB layout. Added revised LWIP Master Demo for STM32F769 discovery board, which has been confirmed to work by setting up at web page.
2021-02-13 Added further documentation in ReadMe. Added status LEDs to Master.
2021-02-14 Added Slave demo program for use with STM32L412RB Nucleo board.
2021-02-16 Updated ReadMe to reflect new name.
2021-08-16 Made changes to folder structure, added documentation.
2021-08-30 Minor changes to PCBs, created demo for wireless communication.
2022-04-23 Merge of recent changes to default master (#1)
    * Made changes to folder structure, added documentation.
    * Minor changes to PCBs, created demo for wireless communication.
2022-05-02 Added documentation.
2022-08-03 Ready for slave demos.

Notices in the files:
parts and their libraries:
Copyright 2016 Accelerated Designs. All rights reserved.
